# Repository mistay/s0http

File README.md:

# s0http
device for uploading counted s0 impulses to your webserver (selfhosted)

## board (PCB)
look at the [eagle/](https://github.com/mistay/s0http/tree/master/eagle) directory. You can either make the board by yourself or order a pcb where you'll get 4 to 5 circuits. They have to be cut and drilled by yourself.

## Arduino Source Code
look at [s0http/](https://github.com/mistay/s0http/tree/master/s0http) directory

## BOM (bill of material)
- [optional 1 pc din rail 12v power supply](http://www.pollin.de/shop/dt/OTc1ODQ2OTk-/Stromversorgung/Netzgeraete/Festspannungs_Netzgeraete/Hutschienen_Schaltnetzteil_MEANWELL_DR_15_12_12_V_1_25_A.html) (approx. 11EUR)
- board, pcb (build by yourself or order here at 20 EUR)
- [1 pc din rail 2TE housing at pollin](http://www.pollin.de/shop/dt/NDU4OTM1OTk-/Bauelemente_Bauteile/Gehaeuse/Hutschienengehaeuse_2_C_35x71x90_mm.html)
 (approx. 4EUR)
- [1 pc mini 360 DC-DC Buck Converter](http://www.ebay.de/sch/i.html?_odkw=step+down&_sop=15&_osacat=0&_from=R40&_trksid=p2045573.m570.l1313.TR11.TRC1.A0.H0.XMini-360+DC-DC+Buck+Konverter.TRS0&_nkw=Mini-360+DC-DC+Buck+Konverter&_sacat=0) (approx. 1EUR)
- [1 pc arduino pro mini](http://www.ebay.de/sch/i.html?_from=R40&_sacat=0&_nkw=pro+mini+arduino&_sop=15) (approx. 2EUR)
- [10 pc mosfet 7002](http://www.ebay.de/sch/i.html?_from=R40&_sacat=0&_sop=15&_nkw=mosfet+7002+SOT-23&rt=nc&LH_BIN=1) (<1EUR)
- [10 pc 10kohm resitors](http://www.ebay.de/sch/i.html?_odkw=mosfet+7002+SOT-23&_sop=15&LH_BIN=1&_osacat=0&_from=R40&_trksid=p2045573.m570.l1313.TR5.TRC1.A0.H0.X0805+10k.TRS0&_nkw=0805+10k&_sacat=0) (<1EUR)
- [10 pc screw terminal](http://www.ebay.de/sch/i.html?_odkw=printklemme&_sop=15&LH_BIN=1&_osacat=0&_from=R40&_trksid=p2045573.m570.l1313.TR3.TRC1.A0.H0.XAnschlussklemme+DG301.TRS0&_nkw=Anschlussklemme+DG301&_sacat=0) (<1EUR)
- [1pc header 40pin](http://www.ebay.de/sch/i.html?_odkw=stiftleiste+header&_sop=15&LH_BIN=1&_osacat=0&_from=R40&_trksid=p2045573.m570.l1313.TR6.TRC0.A0.H0.Xheader+2.54.TRS0&_nkw=header+2.54&_sacat=0) (<1EUR)

## special thanks
to einstein st0nie st0ne.

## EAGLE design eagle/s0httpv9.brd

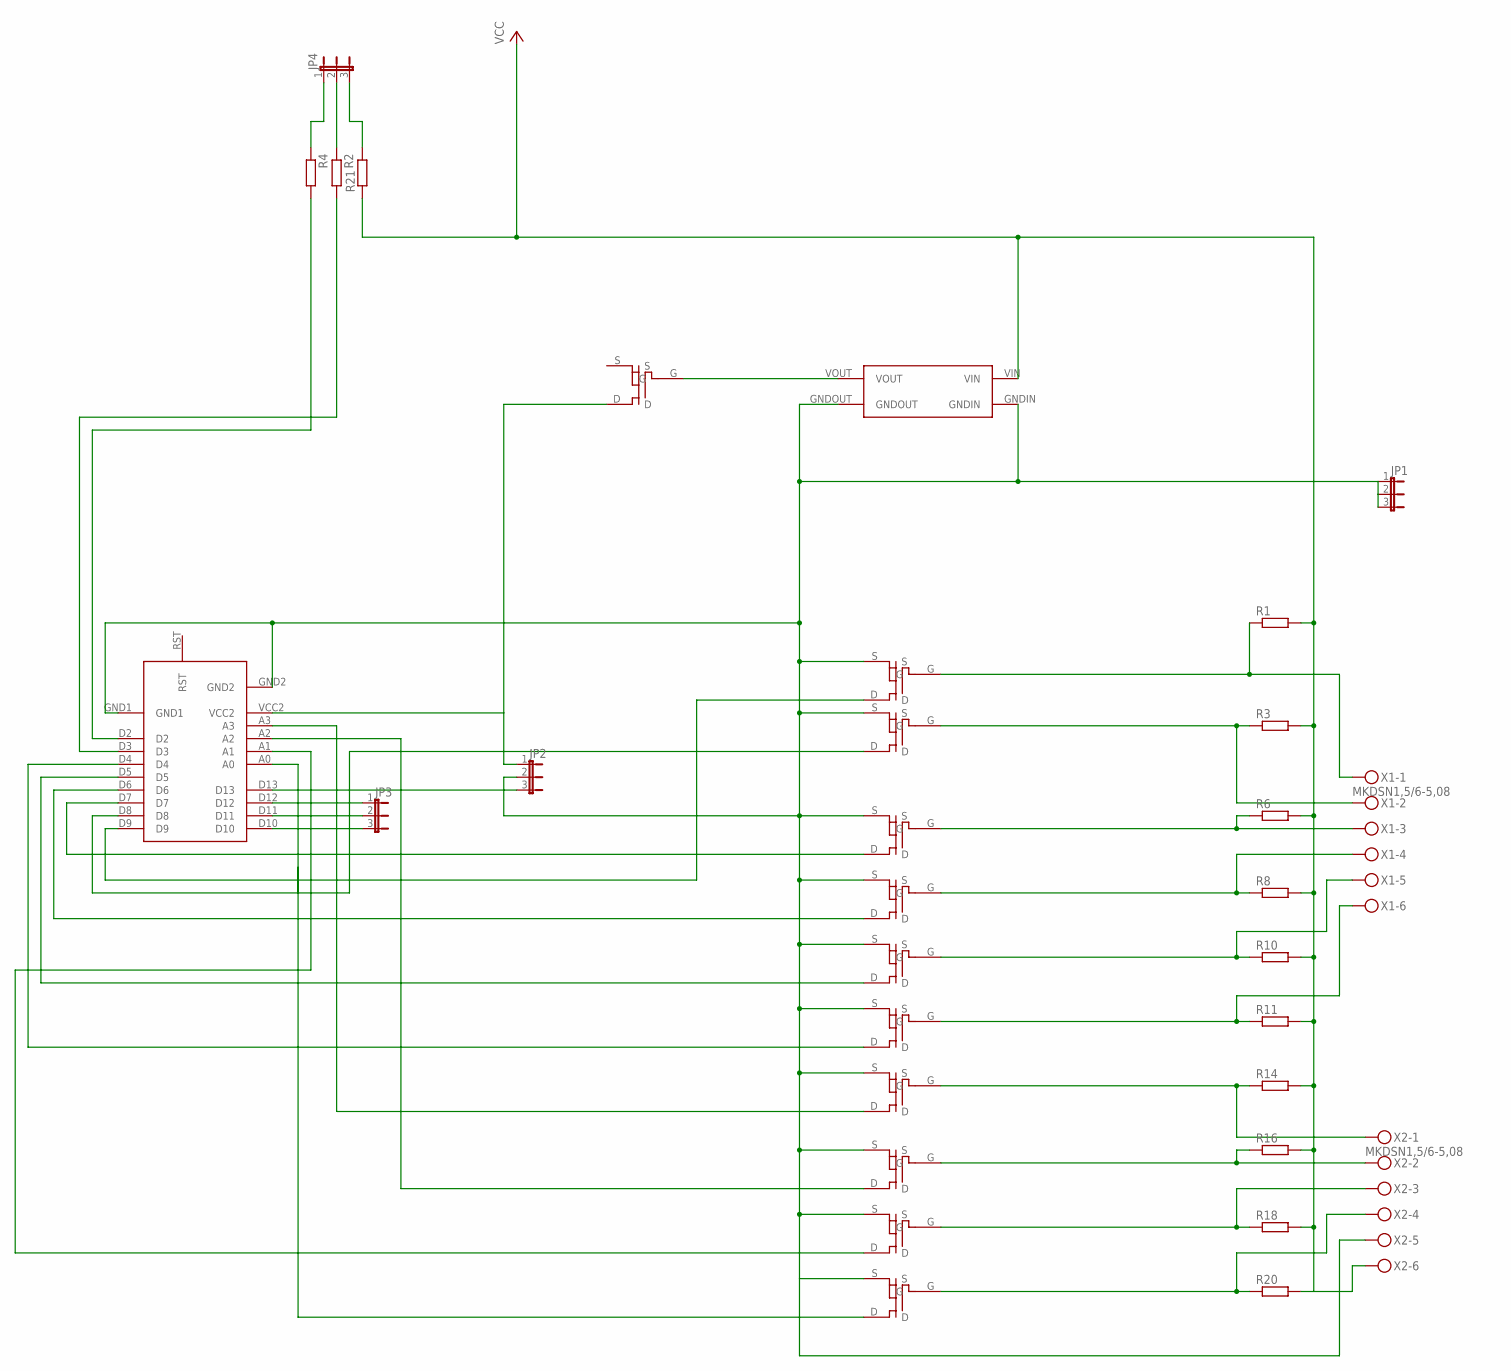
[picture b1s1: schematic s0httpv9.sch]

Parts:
JP1, JP2, JP3, JP4: JP2E; JP2
R1, R2, R3, R4, R6, R8, R10, R11, R14, R16, R18, R20, R21: R-EU_R0805; R0805
U$1: ARDUINOPROMINIREDUCED
U$2: VREGMODULE
U$3, U$4, U$5, U$6, U$7, U$8, U$9, U$10, U$11, U$12, U$13: MOSFET-TO236
X1, X2: MKDSN1,5/6-5,08

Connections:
GND: JP1.1, JP1.2, JP1.3, JP2.2, U$1.GND1, U$1.GND2, U$2.GNDIN, U$2.GNDOUT, U$3.S, U$4.S, U$5.S, U$6.S, U$7.S, U$8.S, U$9.S, U$10.S, U$11.S, U$12.S, X2.5
unnamed: R14.1, U$9.G, X2.1
unnamed: R10.1, U$7.G, X1.5
unnamed: JP3.3, U$1.D10
unnamed: R16.1, U$10.G, X2.2
unnamed: R18.1, U$11.G, X2.3
unnamed: JP3.2, U$1.D11
unnamed: JP3.1, U$1.D12
unnamed: U$1.D8, U$4.D
unnamed: JP2.3, U$1.D13
unnamed: U$1.D9, U$3.D
unnamed: JP2.1, U$1.VCC2, U$13.D
unnamed: U$1.A3, U$9.D
unnamed: U$1.D6, U$6.D
unnamed: U$1.D5, U$7.D
unnamed: U$1.A2, U$10.D
unnamed: U$1.D4, U$8.D
unnamed: U$1.D7, U$5.D
unnamed: U$2.VOUT, U$13.G
unnamed: U$1.A0, U$12.D
unnamed: R1.1, U$3.G, X1.1
unnamed: R3.1, U$4.G, X1.2
unnamed: U$1.A1, U$11.D
unnamed: R6.1, U$5.G, X1.3
unnamed: R8.1, U$6.G, X1.4
unnamed: R11.1, U$8.G, X1.6
unnamed: JP4.3, R21.2
unnamed: R20.1, U$12.G, X2.4
unnamed: JP4.1, R4.1
unnamed: JP4.2, R2.1
unnamed: R2.2, U$1.D3
unnamed: R4.2, U$1.D2
VCC: R1.2, R3.2, R6.2, R8.2, R10.2, R11.2, R14.2, R16.2, R18.2, R20.2, R21.1, U$2.VIN, X2.6

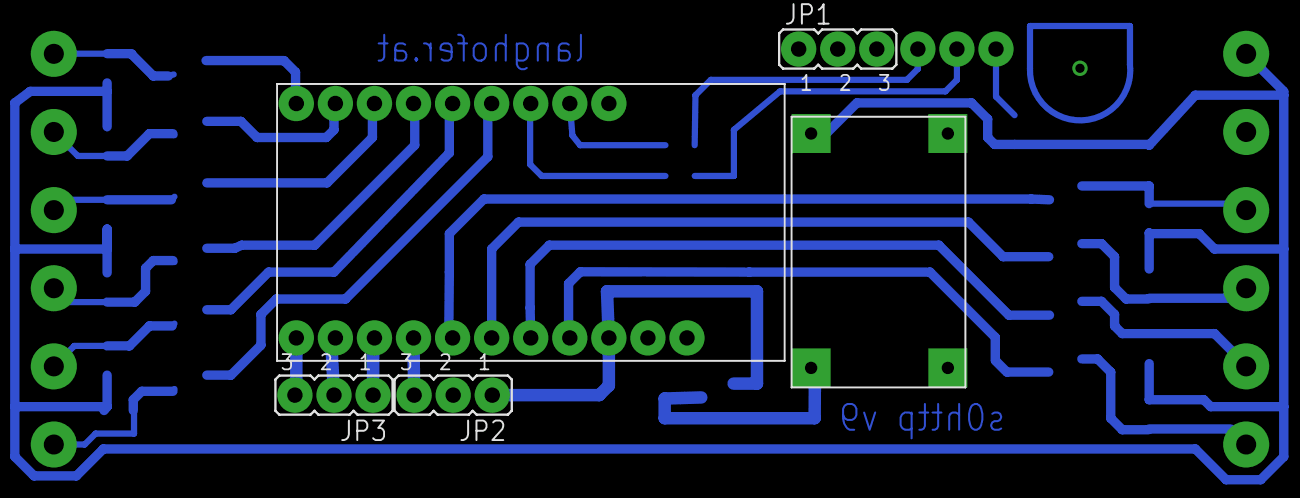
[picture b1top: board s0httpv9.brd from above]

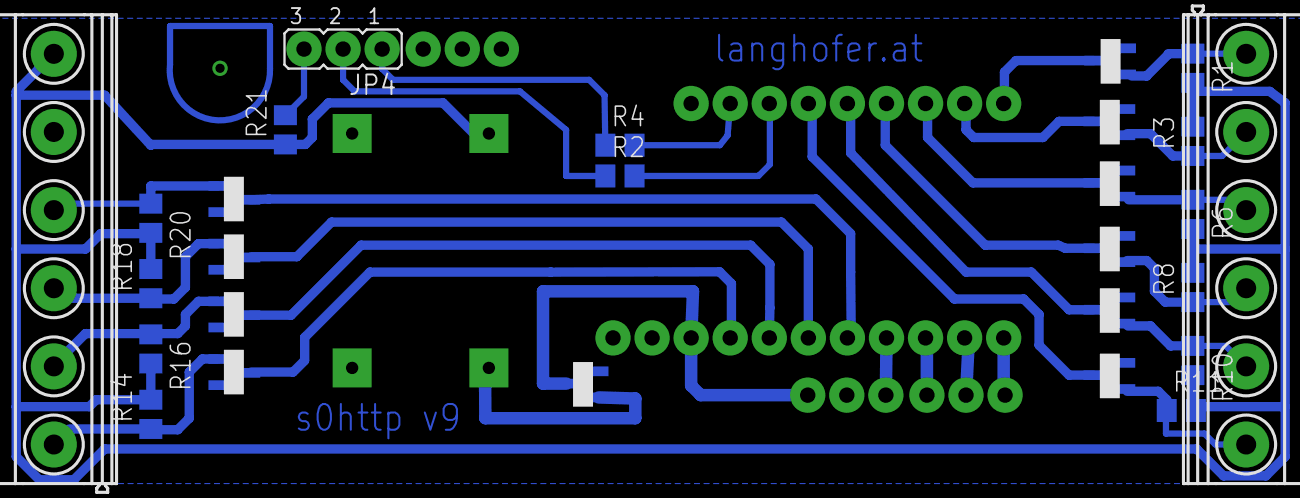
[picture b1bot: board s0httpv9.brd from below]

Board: 2 copper layers, 32 parts (27 on the bottom side), 33 nets.

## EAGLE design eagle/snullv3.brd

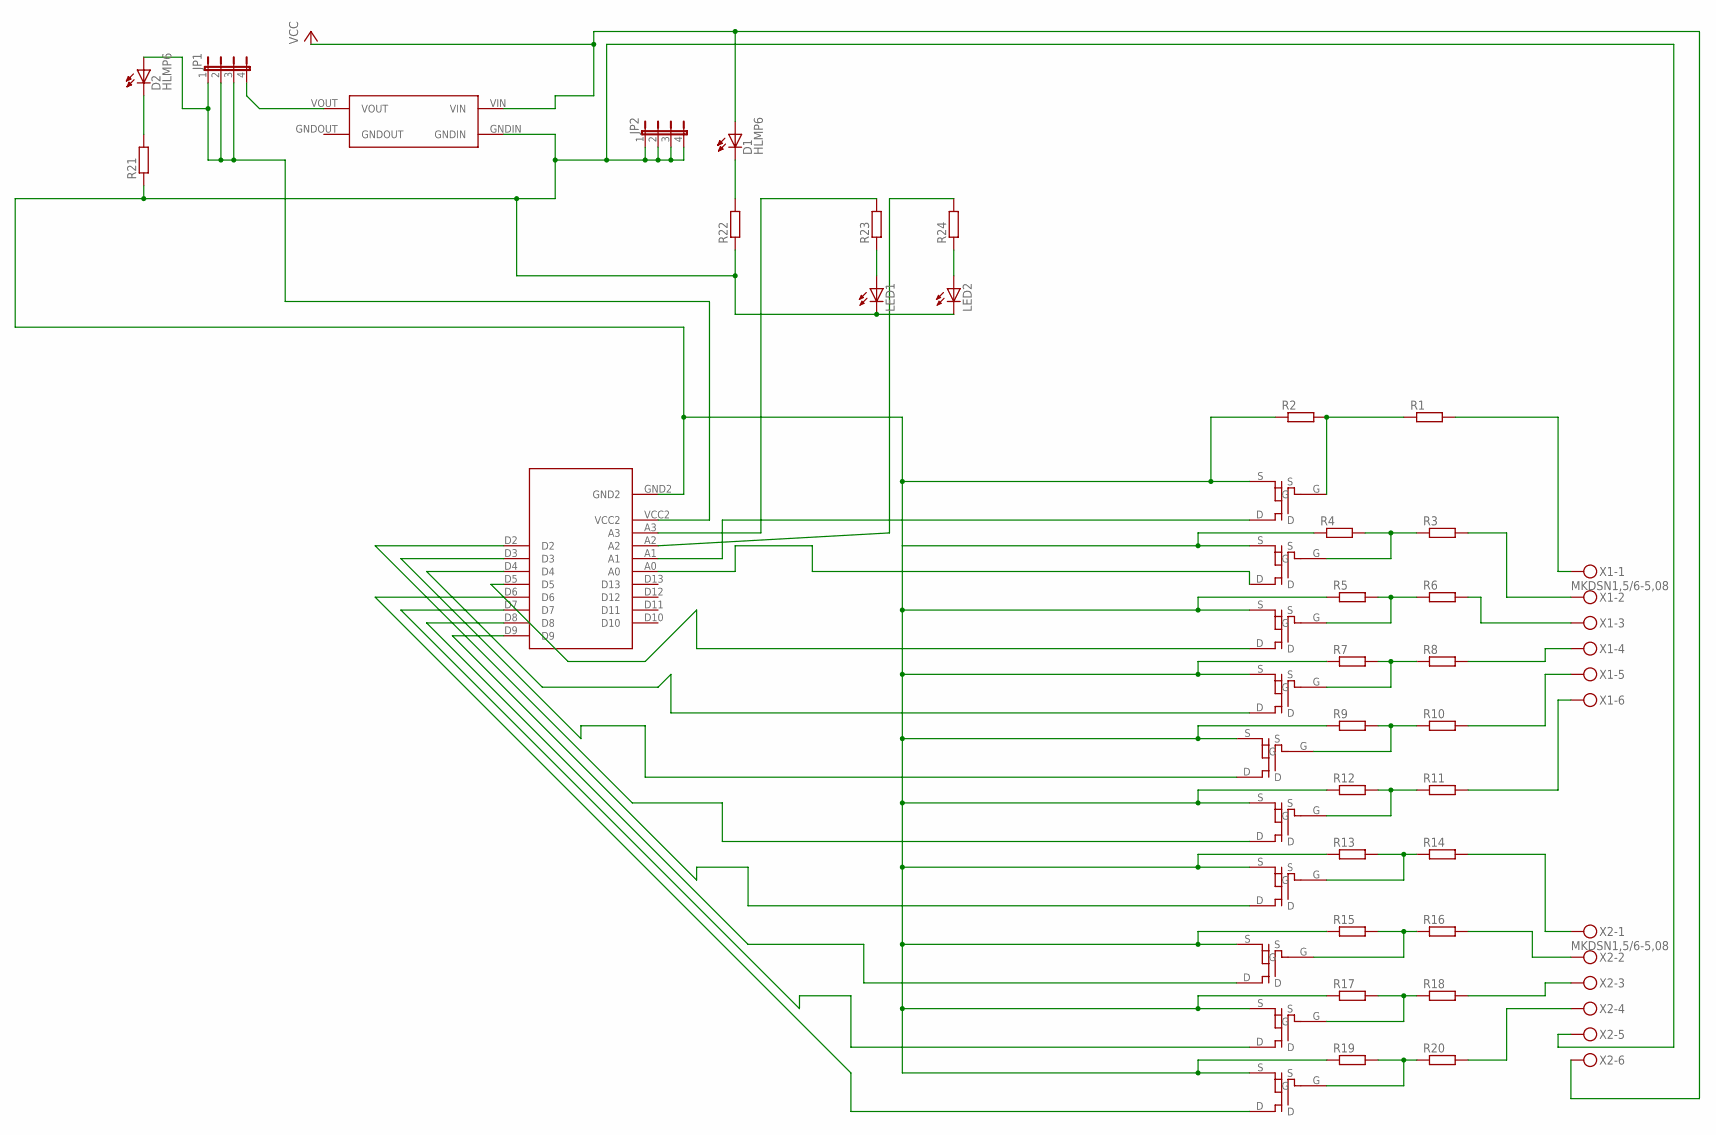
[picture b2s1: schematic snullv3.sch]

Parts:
D1, D2: HLMP6
JP1, JP2: JP4E; JP4
LED1, LED2: LEDCHIP-LED0805; CHIP-LED0805
R1, R2, R3, R4, R5, R6, R7, R8, R9, R10, R11, R12, R13, R14, R15, R16, R17, R18, R19, R20, R21, R22, R23, R24: R-EU_R0805; R0805
U$1: ARDUINOPROMINIREDUCED
U$2: VREGMODULE
U$3, U$4, U$5, U$6, U$7, U$8, U$9, U$10, U$11, U$12: MOSFET-TO236
X1, X2: MKDSN1,5/6-5,08

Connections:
unnamed: R13.2, R14.1, U$9.G
unnamed: R6.2, X1.3
unnamed: R14.2, X2.1
unnamed: R16.2, X2.2
unnamed: R18.2, X2.3
unnamed: R1.2, X1.1
unnamed: R8.2, X1.4
unnamed: U$1.A0, U$4.D
unnamed: R9.2, R10.1, U$7.G
unnamed: U$1.A1, U$3.D
unnamed: R3.2, X1.2
unnamed: D2.A, JP1.1, JP1.2, JP1.3, U$1.VCC2
unnamed: U$1.D9, U$9.D
unnamed: U$1.D4, U$6.D
unnamed: U$1.D3, U$7.D
unnamed: U$1.D8, U$10.D
unnamed: U$1.D2, U$8.D
unnamed: U$1.D5, U$5.D
unnamed: JP1.4, U$2.VOUT
unnamed: R10.2, X1.5
unnamed: U$1.D6, U$12.D
unnamed: R1.1, R2.2, U$3.G
unnamed: U$1.D7, U$11.D
unnamed: R5.2, R6.1, U$5.G
unnamed: R3.1, R4.2
unnamed: R7.2, R8.1, U$6.G
unnamed: R11.2, X1.6
unnamed: R11.1, R12.2, U$8.G
unnamed: R20.2, X2.4
unnamed: R19.2, R20.1, U$12.G
unnamed: R17.2, R18.1, U$11.G
unnamed: R15.2, R16.1, U$10.G
unnamed: D2.K, R21.2
unnamed: D1.K, R22.2
unnamed: LED1.A, R23.1
unnamed: LED2.A, R24.1
unnamed: R23.2, U$1.A3
unnamed: R24.2, U$1.A2
VCC: D1.A, U$2.VIN, X2.6
VDD: JP2.1, JP2.2, JP2.3, JP2.4, LED1.C, LED2.C, R2.1, R4.1, R5.1, R7.1, R9.1, R12.1, R13.1, R15.1, R17.1, R19.1, R21.1, R22.1, U$1.GND2, U$2.GNDIN, U$3.S, U$4.S, U$5.S, U$6.S, U$7.S, U$8.S, U$9.S, U$10.S, U$11.S, U$12.S, X2.5

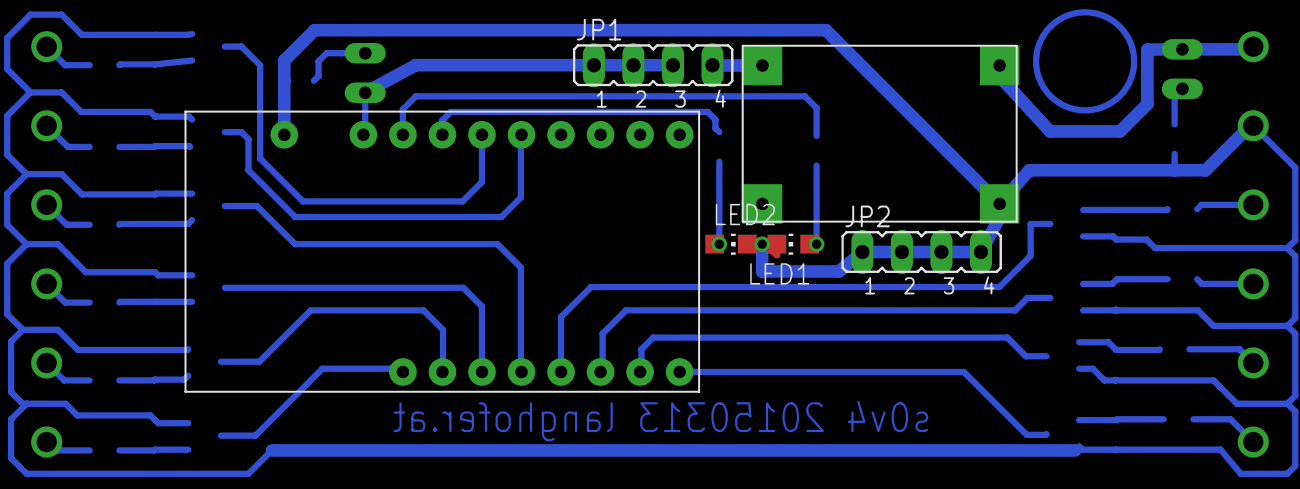
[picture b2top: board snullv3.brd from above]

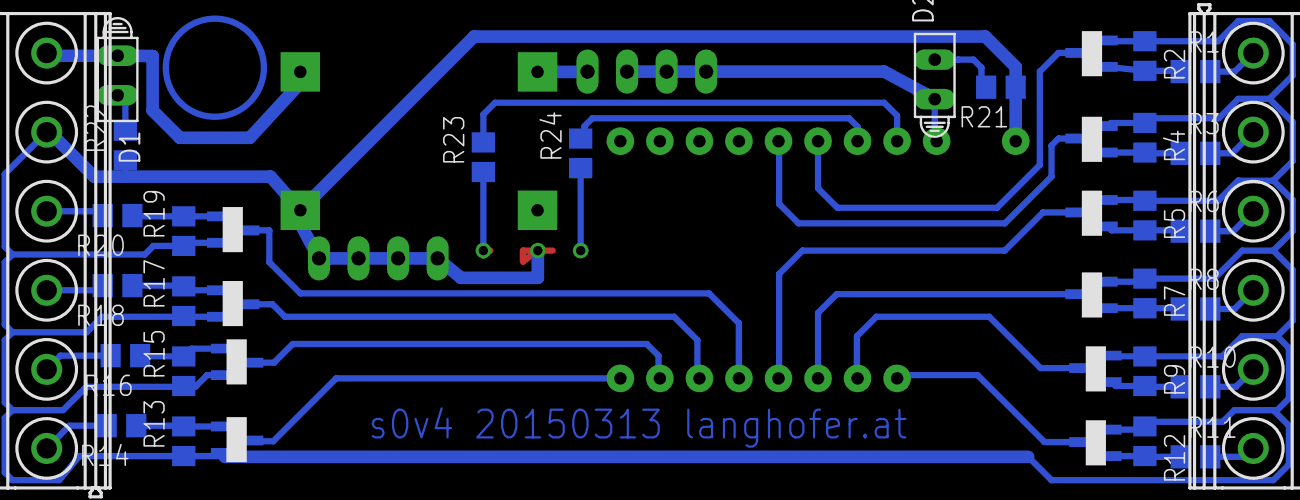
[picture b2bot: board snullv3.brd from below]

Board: 2 copper layers, 44 parts (38 on the bottom side), 40 nets.

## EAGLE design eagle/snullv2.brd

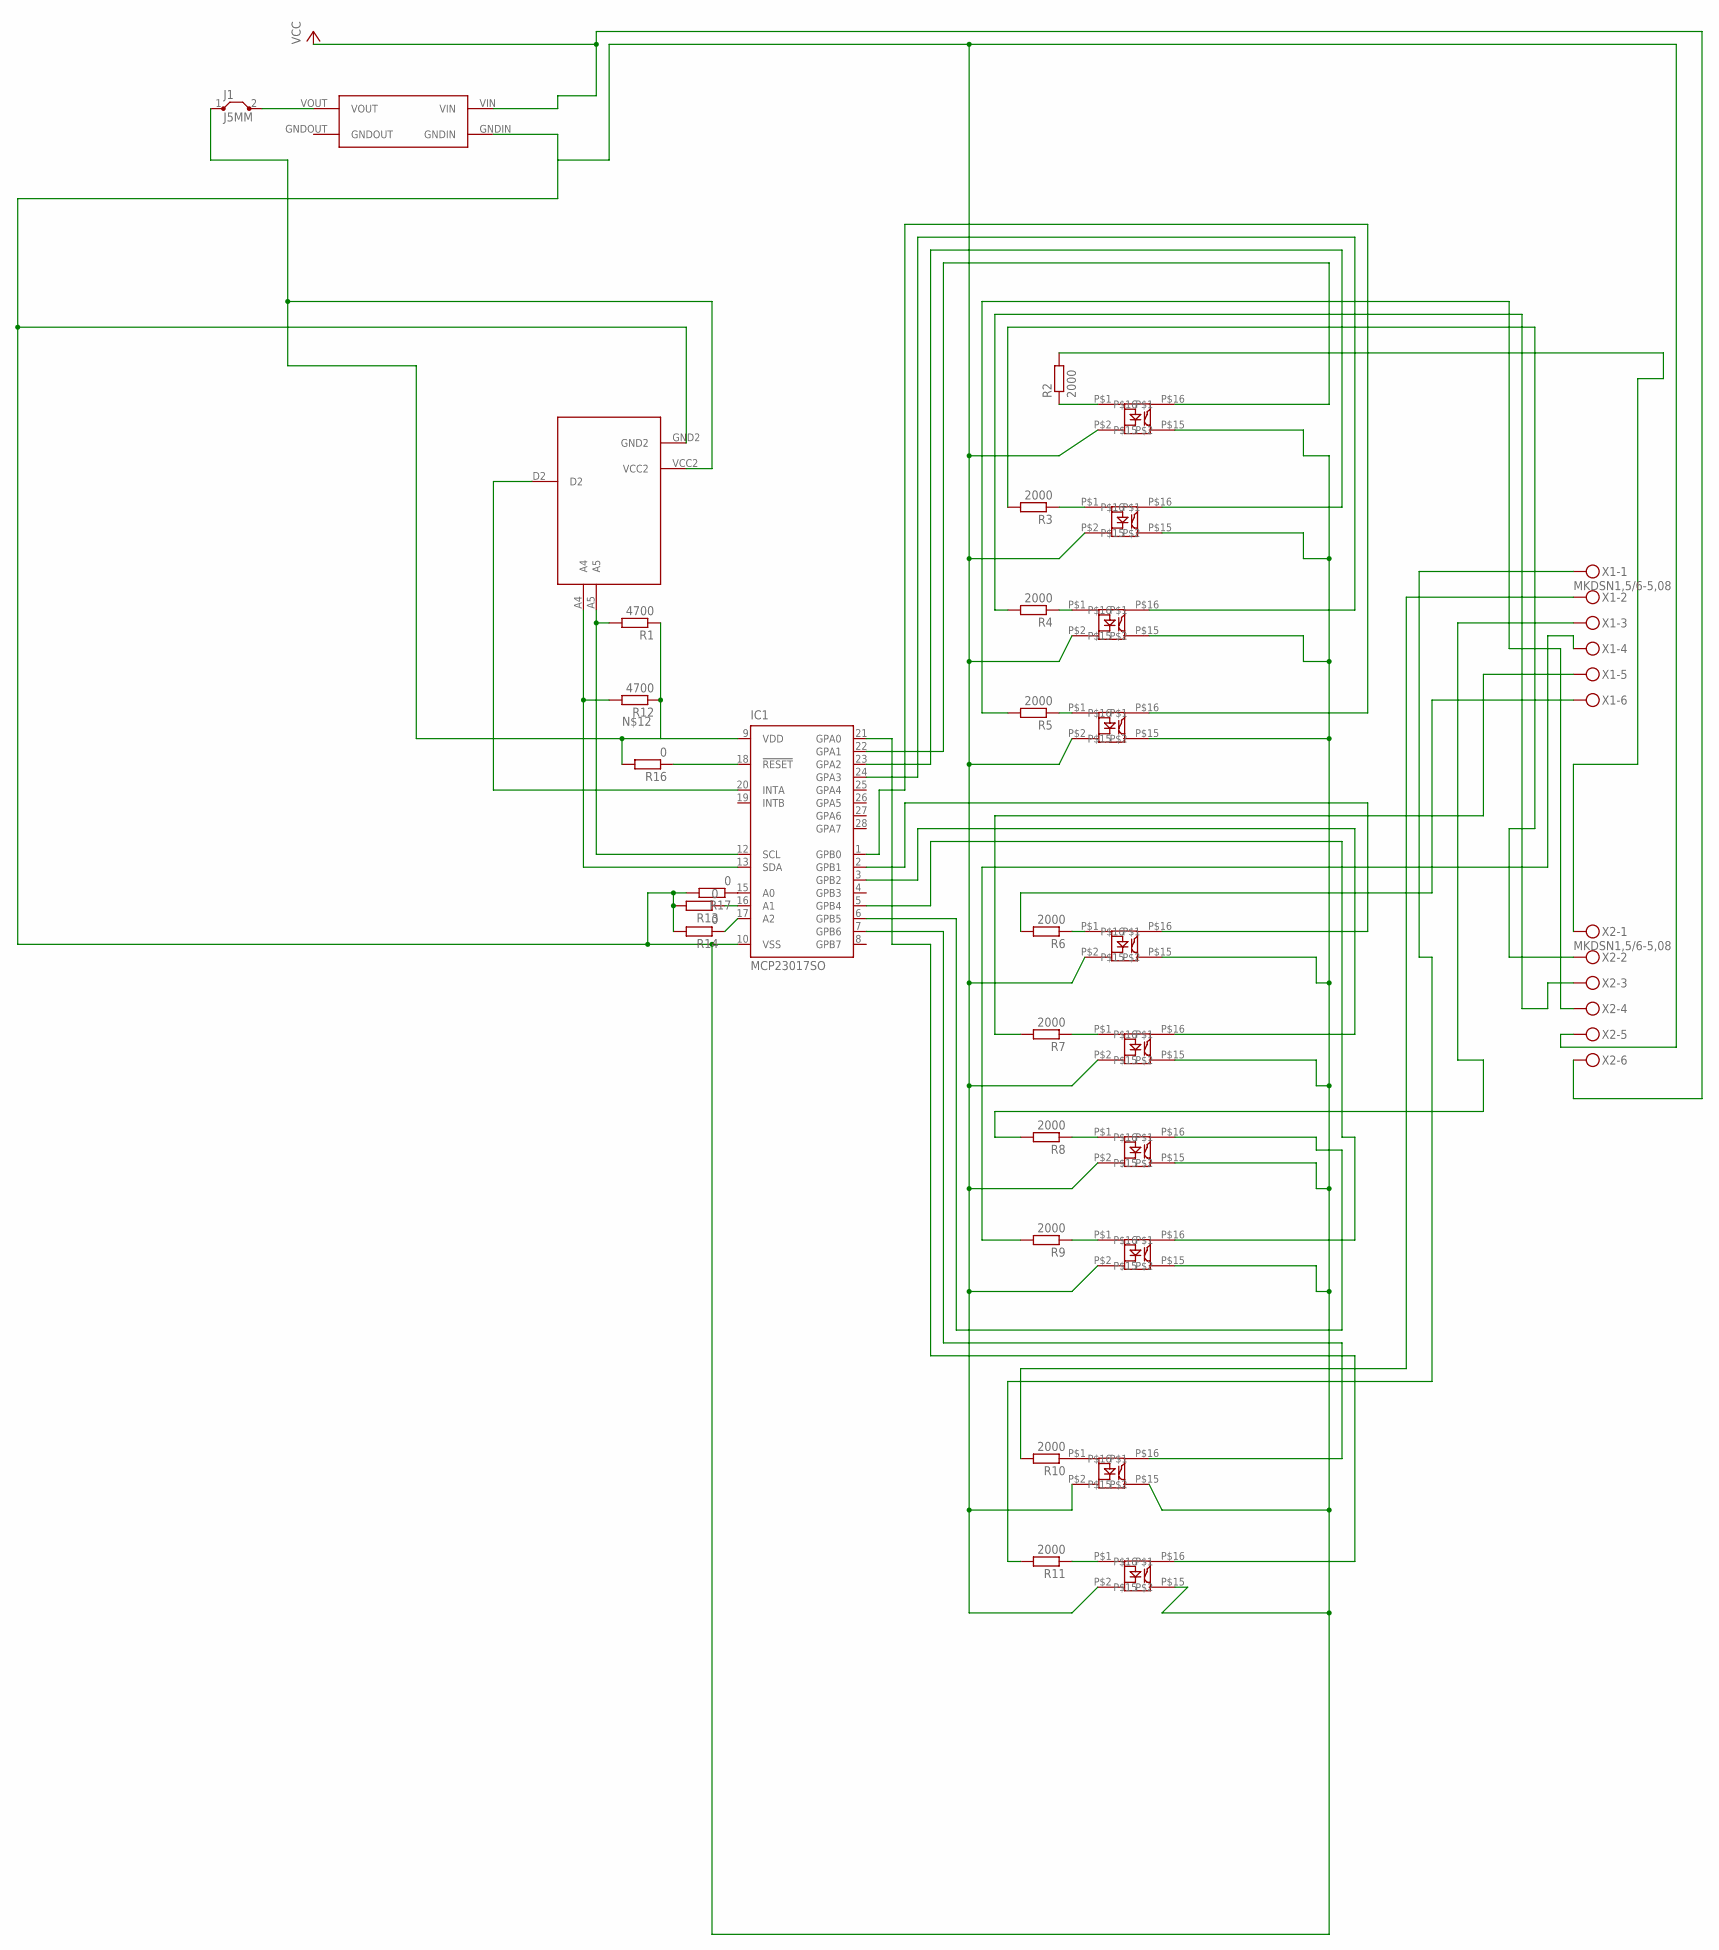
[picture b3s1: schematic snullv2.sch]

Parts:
IC1: MCP23017SO; SO28W
J1: J5MM; 05
R1, R12: 4700; R0805
R2, R3, R4, R5, R6, R7, R8, R9, R10, R11: 2000; R0805
R13, R14, R16, R17: 0; R0805
U$1: ARDUINOPROMINIREDUCED
U$3, U$4, U$6, U$7, U$8, U$9, U$10, U$11, U$12, U$13: OPTO1CHAN
U$5: VREGMODULE
X1, X2: MKDSN1,5/6-5,08

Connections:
unnamed: R11.1, U$13.P$1
unnamed: R6.1, U$8.P$1
unnamed: R7.1, U$9.P$1
unnamed: R8.1, U$10.P$1
unnamed: R9.1, U$11.P$1
unnamed: R10.1, U$12.P$1
unnamed: R5.1, U$7.P$1
unnamed: R4.1, U$6.P$1
unnamed: R3.1, U$4.P$1
unnamed: R2.1, U$3.P$1
unnamed: IC1.13 (SDA), R12.2, U$1.A4
unnamed: IC1.9 (VDD), J1.1, R1.1, R12.1, R16.2, U$1.VCC2
unnamed: IC1.17 (A2), R14.1
unnamed: IC1.18 (!RESET), R16.1
unnamed: IC1.20 (INTA), U$1.D2
unnamed: R6.2, X1.6
unnamed: R9.2, X1.4
unnamed: R8.2, X1.3
unnamed: J1.2, U$5.VOUT
unnamed: IC1.15 (A0), R17.1
unnamed: IC1.16 (A1), R13.1
unnamed: IC1.12 (SCL), R1.2, U$1.A5
unnamed: R3.2, X2.2
unnamed: R4.2, X2.3
unnamed: R5.2, X2.4
unnamed: R7.2, X1.5
unnamed: R2.2, X2.1
unnamed: R10.2, X1.2
unnamed: R11.2, X1.1
unnamed: IC1.22 (GPA1), U$3.P$16
unnamed: IC1.23 (GPA2), U$4.P$16
unnamed: IC1.24 (GPA3), U$6.P$16
unnamed: IC1.1 (GPB0), U$7.P$16
unnamed: IC1.2 (GPB1), U$8.P$16
unnamed: IC1.3 (GPB2), U$9.P$16
unnamed: IC1.5 (GPB4), U$11.P$16
unnamed: IC1.6 (GPB5), U$10.P$16
unnamed: IC1.7 (GPB6), U$12.P$16
unnamed: IC1.21 (GPA0), U$13.P$16
VCC: U$5.VIN, X2.6
VDD: IC1.10 (VSS), R13.2, R14.2, R17.2, U$1.GND2, U$3.P$2, U$3.P$15, U$4.P$2, U$4.P$15, U$5.GNDIN, U$6.P$2, U$6.P$15, U$7.P$2, U$7.P$15, U$8.P$2, U$8.P$15, U$9.P$2, U$9.P$15, U$10.P$2, U$10.P$15, U$11.P$2, U$11.P$15, U$12.P$2, U$12.P$15, U$13.P$2, U$13.P$15, X2.5

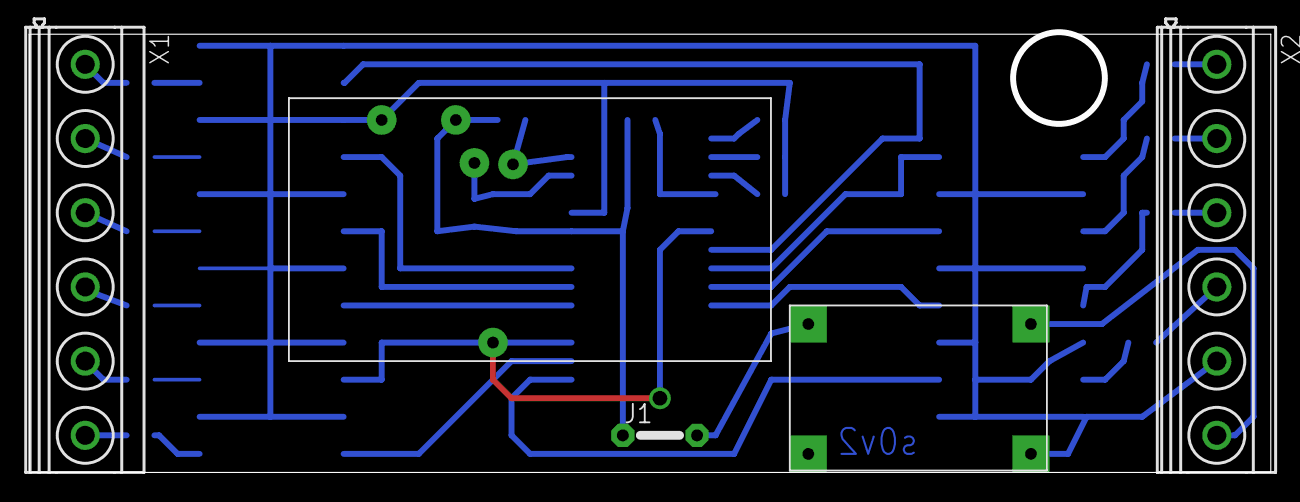
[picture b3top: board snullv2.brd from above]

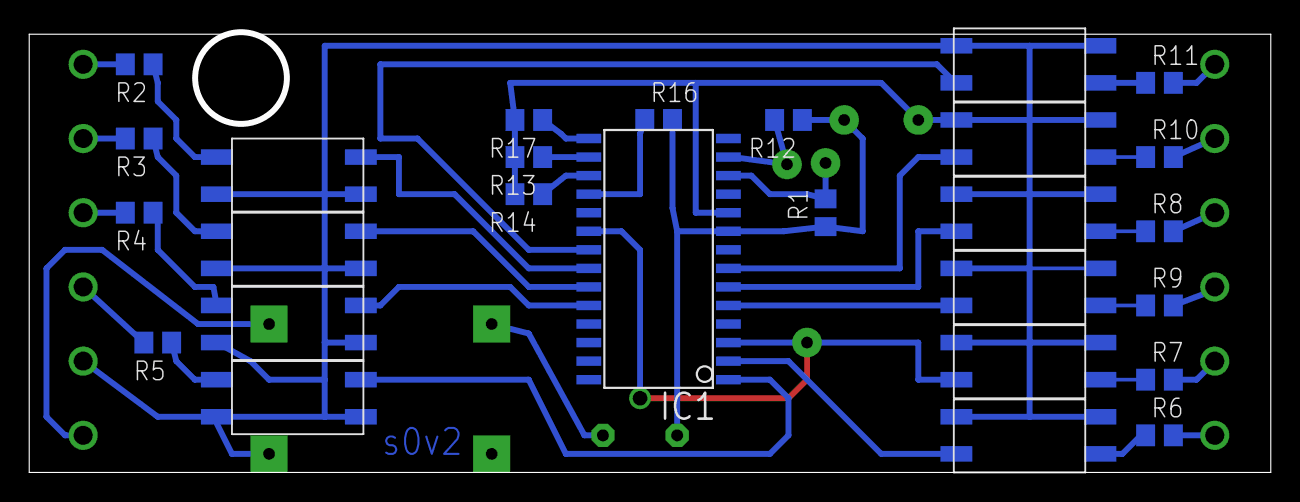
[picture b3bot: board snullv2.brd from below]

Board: 2 copper layers, 84.6 x 29.9 mm, 32 parts (27 on the bottom side), 41 nets.

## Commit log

2015-04-12 init commit
2015-04-20 added v8, added stiker, updated pinning in sketch
2015-04-21 added v9
2015-04-21 blah
2015-04-21 updated project
2015-05-12 added media
2015-05-13 added vz
2015-05-22 cleaned up eagle directory
2015-05-22 added some pictures and lcd touchscreen videos
2015-05-22 schematic cleanup and tagging as v9
2015-05-22 removed v8
2015-05-22 changed to 0.6 thicknes for most connections
2015-06-16 init
2016-02-09 sticker: added MAC field, updated SW rev on label
2016-03-07 media: added some fotos, updated sticker w/ mac address
